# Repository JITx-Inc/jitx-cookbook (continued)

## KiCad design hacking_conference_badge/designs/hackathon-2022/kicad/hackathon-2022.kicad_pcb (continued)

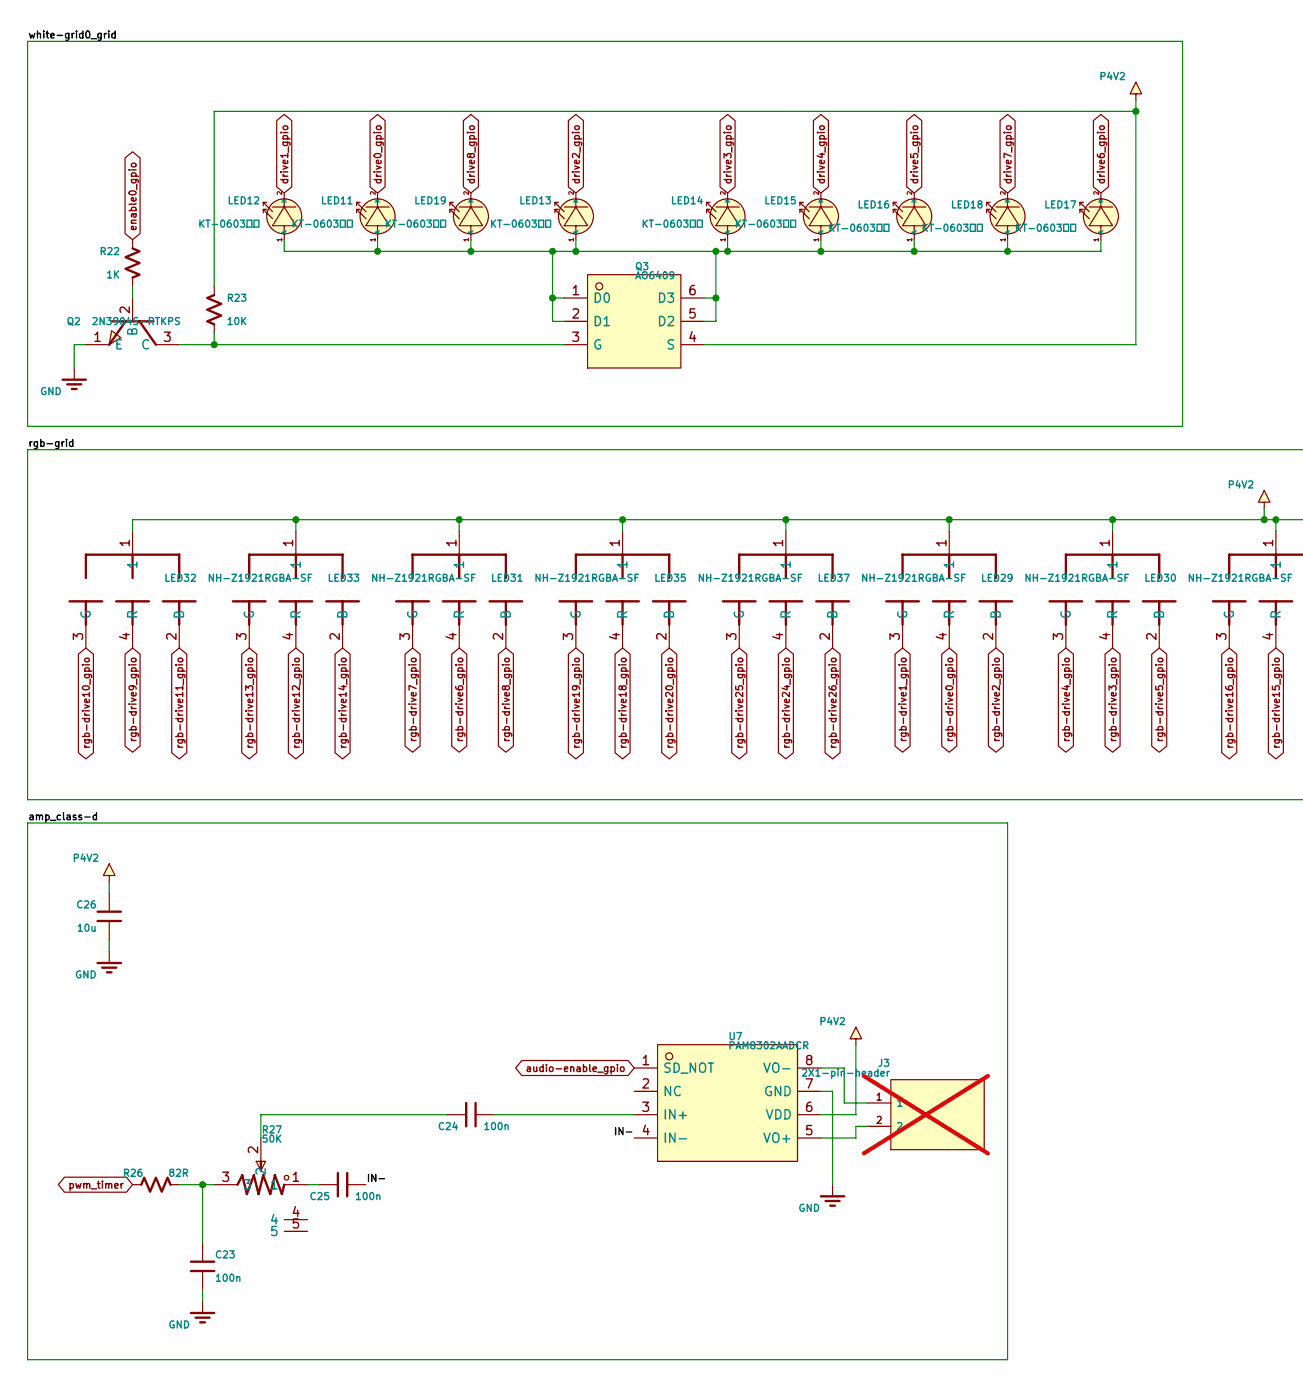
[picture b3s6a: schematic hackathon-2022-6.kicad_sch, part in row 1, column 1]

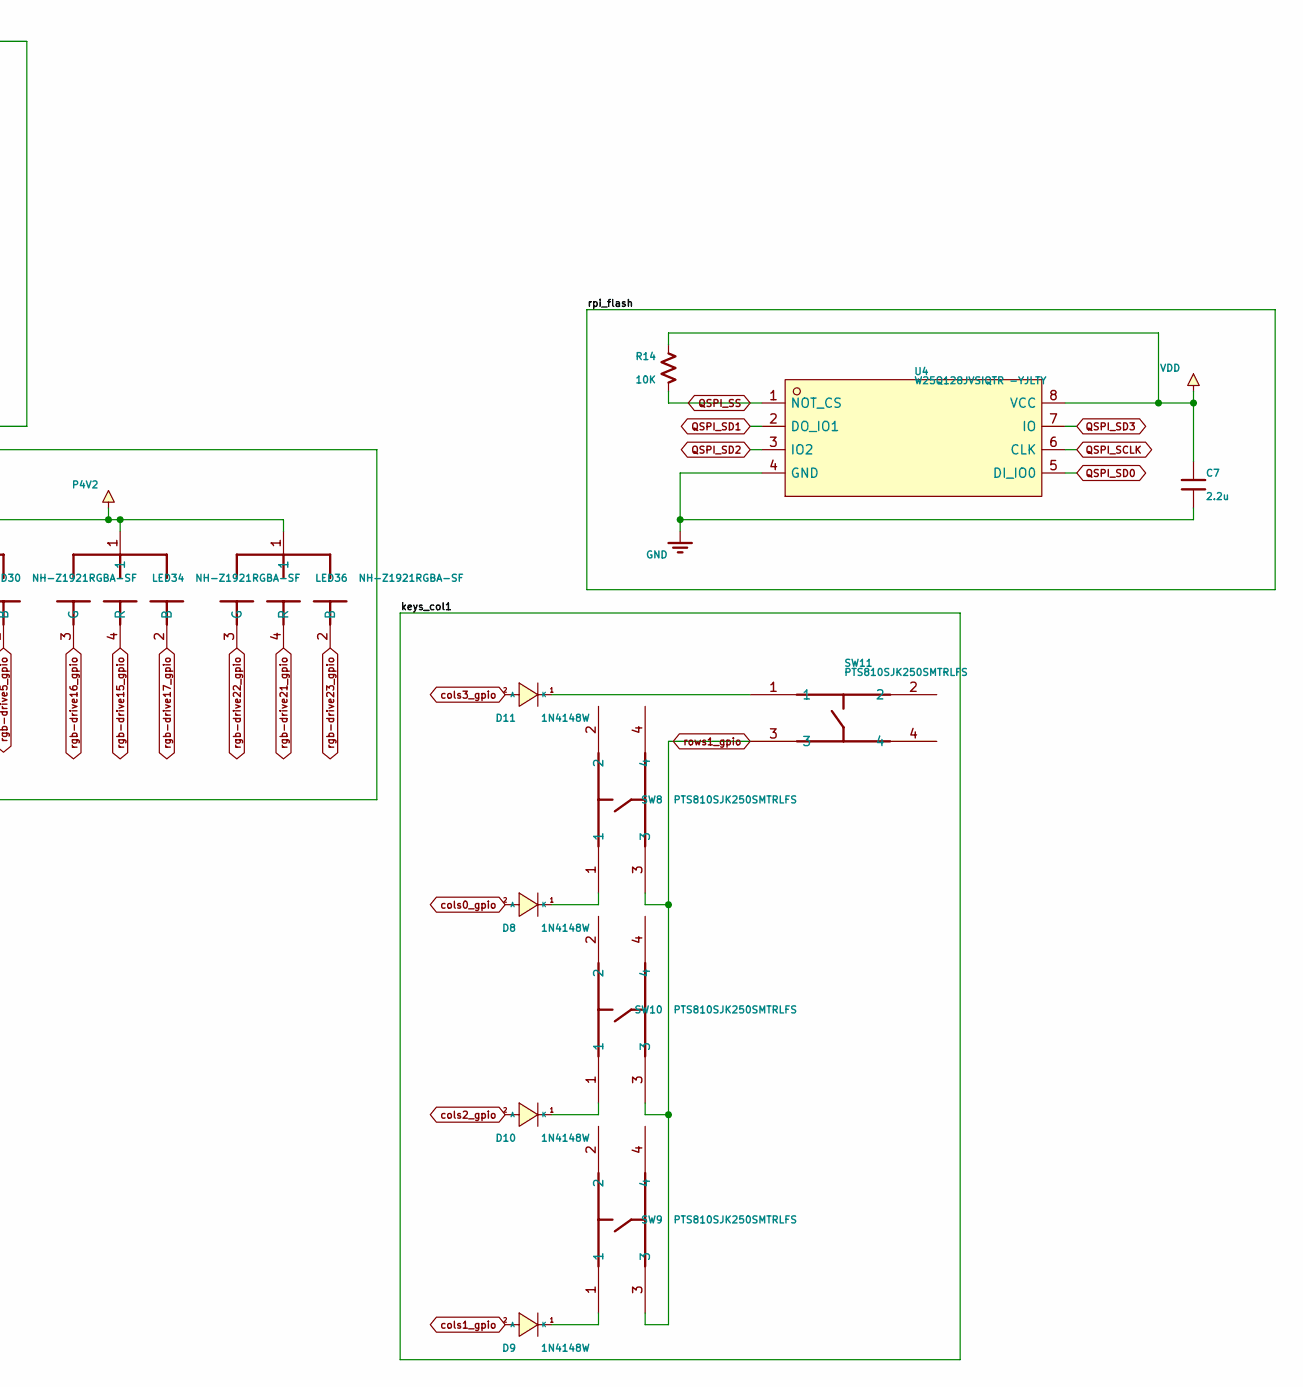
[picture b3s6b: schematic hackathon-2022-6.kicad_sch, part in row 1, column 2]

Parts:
C7: 2.2u; Pkg0402_5; MPN C1005X5R1E225K050BE
C23, C24, C25: 100n; Pkg0402_2; MPN CL05B104KA5NNNC
C26: 10u; Pkg0402_5; MPN CL05A106MP5NUNC
D8: 1N4148W; SOD_123F_L2_7_W1_6_LS3_8_RD_6; MPN 1N4148W; LCSC C81598
D9: 1N4148W; SOD_123F_L2_7_W1_6_LS3_8_RD_4; MPN 1N4148W; LCSC C81598
D10: 1N4148W; SOD_123F_L2_7_W1_6_LS3_8_RD_2; MPN 1N4148W; LCSC C81598
D11: 1N4148W; SOD_123F_L2_7_W1_6_LS3_8_RD_7; MPN 1N4148W; LCSC C81598
J3: 2X1-pin-header; PIN_GRID; MPN 2X1-pin-header; not fitted
LED11, LED12, LED13, LED14, LED15, LED16, LED17, LED18, LED19: KT-0603白灯; LED0603_R_RD_WHITE; MPN KT-0603白灯; LCSC C2290
LED29, LED30, LED31, LED32, LED33, LED34, LED35, LED36, LED37: NH-Z1921RGBA-SF; LED_ARRAY_SMD_4P_L2_2_W2_1_BR; MPN NH-Z1921RGBA-SF; LCSC C2874119
Q2: 2N3904S-RTKPS; SOT_23_3_L2_9_W1_3_P1_90_LS2_4_TR; MPN 2N3904S-RTKPS; LCSC C18536
Q3: AO6409; TSOP_6_L3_0_W1_5_P0_95_LS2_8_BR; MPN AO6409; LCSC C115833
R14: 10K; Pkg0402_1; MPN ESR01MZPJ103
R22: 1K; Pkg0402_1; MPN SG73P1EWTTP1001F
R23: 10K; Pkg0402_1; MPN RC1005F103CS
R26: 82R; Pkg0402_1; MPN RMCF0402FT82R0
R27: 50K; RES_TH_RK09K1130AAU_1; MPN RK09K1130ACL; LCSC C470291
SW8: PTS810SJK250SMTRLFS; KEY_SMD_4P_L4_2_W3_2_P2_20_LS4_6_1; MPN PTS810SJK250SMTRLFS; LCSC C221896
SW9: PTS810SJK250SMTRLFS; KEY_SMD_4P_L4_2_W3_2_P2_20_LS4_6_8; MPN PTS810SJK250SMTRLFS; LCSC C221896
SW10: PTS810SJK250SMTRLFS; KEY_SMD_4P_L4_2_W3_2_P2_20_LS4_6_6; MPN PTS810SJK250SMTRLFS; LCSC C221896
SW11: PTS810SJK250SMTRLFS; KEY_SMD_4P_L4_2_W3_2_P2_20_LS4_6_2; MPN PTS810SJK250SMTRLFS; LCSC C221896
U4: W25Q128JVSIQTR -YJLTY; SOIC_8_L5_3_W5_3_P1_27_LS8_0_BL; MPN W25Q128JVSIQTR -YJLTY; LCSC C2921483
U7: PAM8302AADCR; SOP_8_L4_9_W3_9_P1_27_LS6_0_BL; MPN PAM8302AADCR; LCSC C112137

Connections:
/6: rpi_flash/IN-: C25.2, U7.4 (IN-)
GND: C7.2, C23.2, C26.1, Q2.1 (E), U4.4 (GND), U7.7 (GND); also elsewhere on the board
unnamed: C23.1, R26.2, R27.3
unnamed: C24.1, R27.2
unnamed: C25.1, R27.1
unnamed: D8.1 (K), SW8.1
unnamed: D9.1 (K), SW9.1
unnamed: D10.1 (K), SW10.1
unnamed: D11.1 (K), SW11.1
unnamed: LED11.1 (A), LED12.1 (A), LED13.1 (A), LED14.1 (A), LED15.1 (A), LED16.1 (A), LED17.1 (A), LED18.1 (A), LED19.1 (A), Q3.1 (D0), Q3.2 (D1), Q3.5 (D2), Q3.6 (D3)
unnamed: Q2.2 (B), R22.2
unnamed: Q2.3 (C), Q3.3 (G), R23.1
unnamed: C24.2, U7.3 (IN+)
unnamed: J3.2, U7.5 (VO+)
unnamed: J3.1, U7.8 (VO-)
P4V2: C26.2, LED29.1, LED30.1, LED31.1, LED32.1, LED33.1, LED34.1, LED35.1, LED36.1, LED37.1, Q3.4 (S), R23.2, U7.6 (VDD); also elsewhere on the board
QSPI_SCLK: U4.6 (CLK); also elsewhere on the board
QSPI_SD0: U4.5 (DI_IO0); also elsewhere on the board
QSPI_SD1: U4.2 (DO_IO1); also elsewhere on the board
QSPI_SD2: U4.3 (IO2); also elsewhere on the board
QSPI_SD3: U4.7 (IO); also elsewhere on the board
QSPI_SS: R14.2, U4.1 (NOT_CS); also elsewhere on the board
VDD: C7.1, R14.1, U4.8 (VCC); also elsewhere on the board
audio-enable_gpio: U7.1 (SD_NOT); also elsewhere on the board
cols0_gpio: D8.2 (A); also elsewhere on the board
cols1_gpio: D9.2 (A); also elsewhere on the board
cols2_gpio: D10.2 (A); also elsewhere on the board
cols3_gpio: D11.2 (A); also elsewhere on the board
drive0_gpio: LED11.2 (K); also elsewhere on the board
drive1_gpio: LED12.2 (K); also elsewhere on the board
drive2_gpio: LED13.2 (K); also elsewhere on the board
drive3_gpio: LED14.2 (K); also elsewhere on the board
drive4_gpio: LED15.2 (K); also elsewhere on the board
drive5_gpio: LED16.2 (K); also elsewhere on the board
drive6_gpio: LED17.2 (K); also elsewhere on the board
drive7_gpio: LED18.2 (K); also elsewhere on the board
drive8_gpio: LED19.2 (K); also elsewhere on the board
enable0_gpio: R22.1; also elsewhere on the board
pwm_timer: R26.1; also elsewhere on the board
rgb-drive0_gpio: LED29.4 (R); also elsewhere on the board
rgb-drive1_gpio: LED29.3 (G); also elsewhere on the board
rgb-drive2_gpio: LED29.2 (B); also elsewhere on the board
rgb-drive3_gpio: LED30.4 (R); also elsewhere on the board
rgb-drive4_gpio: LED30.3 (G); also elsewhere on the board
rgb-drive5_gpio: LED30.2 (B); also elsewhere on the board
rgb-drive6_gpio: LED31.4 (R); also elsewhere on the board
rgb-drive7_gpio: LED31.3 (G); also elsewhere on the board
rgb-drive8_gpio: LED31.2 (B); also elsewhere on the board
rgb-drive9_gpio: LED32.4 (R); also elsewhere on the board
rgb-drive10_gpio: LED32.3 (G); also elsewhere on the board
rgb-drive11_gpio: LED32.2 (B); also elsewhere on the board
rgb-drive12_gpio: LED33.4 (R); also elsewhere on the board
rgb-drive13_gpio: LED33.3 (G); also elsewhere on the board
rgb-drive14_gpio: LED33.2 (B); also elsewhere on the board
rgb-drive15_gpio: LED34.4 (R); also elsewhere on the board
rgb-drive16_gpio: LED34.3 (G); also elsewhere on the board
rgb-drive17_gpio: LED34.2 (B); also elsewhere on the board
rgb-drive18_gpio: LED35.4 (R); also elsewhere on the board
rgb-drive19_gpio: LED35.3 (G); also elsewhere on the board
rgb-drive20_gpio: LED35.2 (B); also elsewhere on the board
rgb-drive21_gpio: LED36.4 (R); also elsewhere on the board
rgb-drive22_gpio: LED36.3 (G); also elsewhere on the board
rgb-drive23_gpio: LED36.2 (B); also elsewhere on the board
rgb-drive24_gpio: LED37.4 (R); also elsewhere on the board
rgb-drive25_gpio: LED37.3 (G); also elsewhere on the board
rgb-drive26_gpio: LED37.2 (B); also elsewhere on the board
rows1_gpio: SW8.3, SW9.3, SW10.3, SW11.3; also elsewhere on the board

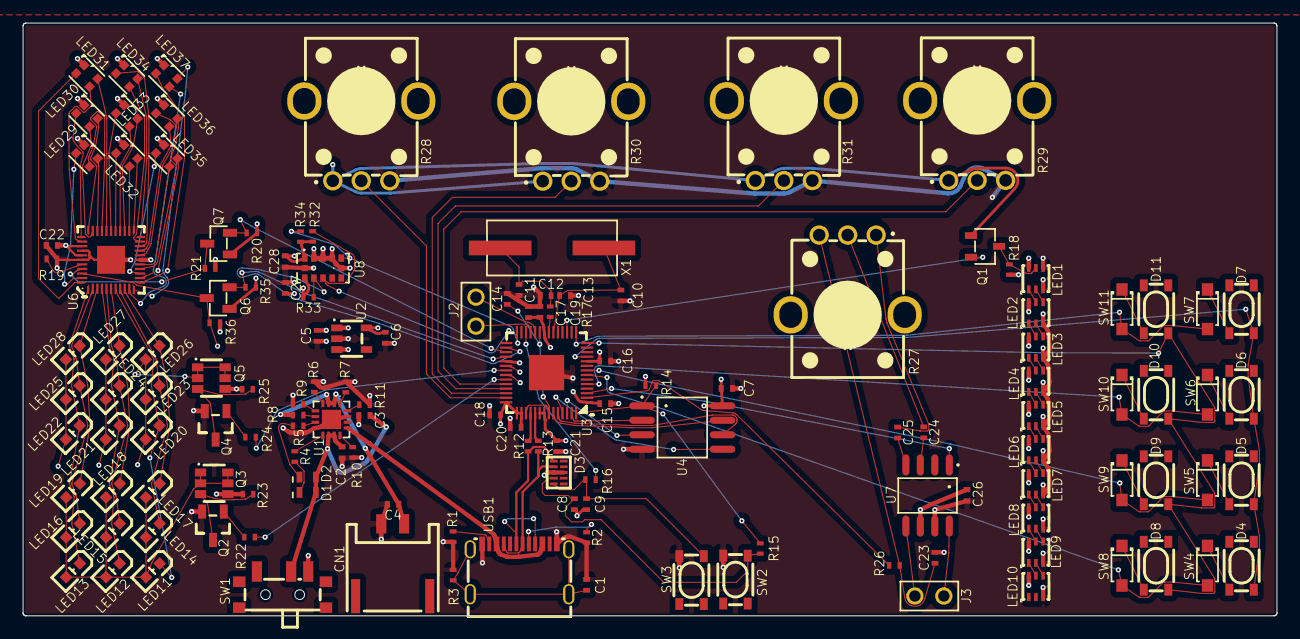
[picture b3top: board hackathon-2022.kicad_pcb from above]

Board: 6 copper layers, 110.0 x 52.0 mm, 142 parts (0 on the bottom side), 137 nets.

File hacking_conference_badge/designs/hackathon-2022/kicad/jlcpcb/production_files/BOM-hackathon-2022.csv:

Comment,Designator,Footprint,LCSC
TAXM12M2GLFBET2T,X1,HC_49S_L11_4_W4_8,C111117
PAM8302AADCR,U7,SOP_8_L4_9_W3_9_P1_27_LS6_0_BL,C112137
AO6409,"Q3,Q5",TSOP_6_L3_0_W1_5_P0_95_LS2_8_BR,C115833
BSN20,Q1,SOT_23_3_L2_9_W1_6_P1_90_LS2_8_BR,C116157
AP2125K-2.8TRG1,U2,SOT_23_5_L3_0_W1_7_P0_95_LS2_8_BR,C176952
2N3904S-RTKPS,"Q2,Q4",SOT_23_3_L2_9_W1_3_P1_90_LS2_4_TR,C18536
PTS810SJK250SMTRLFS,"SW10,SW11,SW2,SW3,SW4,SW5,SW6,SW7,SW8,SW9",KEY_SMD_4P_L4_2_W3_2_P2_20_LS4_6_6,C221896
KT-0603白灯,"LED11,LED12,LED13,LED14,LED15,LED16,LED17,LED18,LED19,LED20,LED21,LED22,LED23,LED24,LED25,LED26,LED27,LED28",LED0603_R_RD_WHITE,C2290
IS31FL3236A-QFLS2-TR,U6,C246443,C246443
NH-Z1921RGBA-SF,"LED29,LED30,LED31,LED32,LED33,LED34,LED35,LED36,LED37",LED_ARRAY_SMD_4P_L2_2_W2_1_BR,C2874119
W25Q128JVSIQTR -YJLTY,U4,SOIC_8_L5_3_W5_3_P1_27_LS8_0_BL,C2921483
PUSB3FR4,D3,DFN2510A_10_L2_5_W1_0_P0_50_BL,C294620
50K,"R27,R28,R29,R30,R31",RES_TH_RK09K1130AAU_1,C470291
BQ24078RGTR,U1,VQFN_16_L3_0_W3_0_P0_50_BL_EP,C473396
PH2.0-2PWB Horizontal,CN1,CONN_SMD_2P_P2_00_PH2_0_SPWB,C47647
TYPE-C-31-M-23,USB1,USB_C_SMD_TYPE_C_31_M_23,C530613
BSS138,"Q6,Q7",SOT_23_3_L2_9_W1_3_P1_90_LS2_4_BR,C713688
MK-12C02-G025,SW1,SW_SMD_MK_12C02_G025,C778186
1N4148W,"D10,D11,D4,D5,D6,D7,D8,D9",SOD_123F_L2_7_W1_6_LS3_8_RD_2,C81598
VL53L0CXV0DH1,U8,OPTO_SMD_12P_VL53L0CXV0DH_1,C91199
WS2816C-2121,"LED1,LED10,LED2,LED3,LED4,LED5,LED6,LED7,LED8,LED9",LED_SMD_6P_L2_2_W2_2_TL_1,C965561
1K,R4,Pkg0402_6,
33R,R8,Pkg0402_6,
2.2u,C7,Pkg0402_5,
10K,R35,Pkg0402_1,
10K,R23,Pkg0402_1,
100n,C27,Pkg0402_2,
100n,C1,Pkg0402_2,
2K,R5,Pkg0402_6,
1u,C5,Pkg0402_2,
33R,R9,Pkg0402_6,
1K,R24,Pkg0402_1,
1u,C18,Pkg0402_2,
10K,R14,Pkg0402_1,
30p,C10,Pkg0402_2,
1u,C14,Pkg0402_2,
10K,R36,Pkg0402_1,
10K,R25,Pkg0402_1,
1u,C6,Pkg0402_2,
1u,C16,Pkg0402_2,
10K,R20,Pkg0402_1,
100n,C23,Pkg0402_2,
"green, Vf 2.0, If 20 mA",D2,Pkg0603,
5K1,R1,Pkg0402_1,
1K1,R10,Pkg0402_4,
RP2040,U3,C2040,
27R,R12,Pkg0402_1,
30p,C11,Pkg0402_2,
1u,C15,Pkg0402_2,
1u,C19,Pkg0402_2,
10u,C26,Pkg0402_5,
1K,R17,Pkg0402_4,
10K,R21,Pkg0402_1,
100n,C24,Pkg0402_2,
5K1,R2,Pkg0402_1,
4.7u,C3,Pkg0402,
2K7,R11,Pkg0402_1,
27R,R13,Pkg0402_1,
100n,C8,Pkg0402_2,
1u,C21,Pkg0402_2,
30p,C12,Pkg0402_2,
33R,R6,Pkg0402_6,
1K,R16,Pkg0402_4,
82R,R26,Pkg0402_1,
8K2,R32,Pkg0402_3,
1u,C20,Pkg0402_2,
1K,R18,Pkg0402_4,
100n,C25,Pkg0402_2,
"red, Vf 2.0, If 20 mA",D1,Pkg0603,
3K3,R19,Pkg0402_1,
8K2,R34,Pkg0402_3,
30p,C13,Pkg0402_2,
8K2,R33,Pkg0402_3,
10K,R7,Pkg0402_6,
1u,C17,Pkg0402_2,
4.7u,C2,Pkg0402,
1K,R15,Pkg0402_4,
100n,C9,Pkg0402_2,
4.7u,C28,Pkg0402_5,
100K,R3,Pkg0402_1,
4.7u,C4,Pkg0402,
2.2u,C22,Pkg0402_5,
1K,R22,Pkg0402_1,

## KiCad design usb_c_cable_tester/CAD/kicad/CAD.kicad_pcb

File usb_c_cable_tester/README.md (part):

# USB-C Cable Tester PCB Cookbook Recipe

This tutorial guides you in creating a USB-C cable testing PCB in JITX from the ground up. With step-by-step instructions, even individuals with no prior experience in JITX can learn to define hardware in software and generate a PCB using code.

## Getting started
##### Prerequisites
To start, we'll need to setup JITX. We can follow this tutorial to get setup: https://docs-testing.jitx.com/faq/installationinstructions.html

Then, we need to create a new project. So let's run VSCode, select the JITX extension, and click "New Project".

Now we're ready to start designing the board.

> NOTE: The code below is not the entire design. Refer to the [Github repo](https://github.com/JITx-Inc/jitx-cookbook/tree/main/usb_c_cable_tester) for a full working design. Below, we describe the design flow and thought process behind designing this board.

##### Intended functionality
Let's start by considering what we want our design to be able to do. It needs to to test every connection in a USB-C cable, and provide feedback about what connections exist, and what connections don't exist, or are broken. To do that, we'll design a circuit board which:

- connects to both ends of a USB-C cable
- sends a signal into the pins of one connector of the cable and should be present on the pins of the other connector
- measures that signal using an LED indicator for every individual USB-C pin. If the LED doesn't light up, it means that the cable has a bad connection

##### Implementation plan

To accomplish the above, we need a few components:

- 2x USB-C connectors, we'll use the [
1054500101 USB-C connector](https://www.lcsc.com/product-detail/span-style-background-color-ff0-USB-span-span-style-background-color-ff0-Connectors-span_MOLEX-1054500101_C134092.html)
- a coin cell battery clip (or similiar battery holder), we'll use the [CR2032 SMD coin cell clip](https://datasheet.lcsc.com/lcsc/1811061923_Q-J-CR2032-BS-6-1_C70377.pdf)
- a number of indicator LEDs

Considering this is a simple design, we'll use a 2 layer board, with all components on the same side for ease of PCBA.

##### Resources

This board is fully open source, available here: [USB-C Cable Tester Recipe](https://github.com/JITx-Inc/jitx-cookbook/tree/main/usb_c_cable_tester)

Clone [this repo](https://github.com/JITx-Inc/jitx-cookbook) and open the subfolder `usb_c_cable_tester` in VSCode to follow along.

## Components

We've identified some specific components that we want to use, namely the [
1054500101 USB-C Connector](https://www.lcsc.com/product-detail/span-style-background-color-ff0-USB-span-span-style-background-color-ff0-Connectors-span_MOLEX-1054500101_C134092.html) and the [CR2032-BS-6-1 Coin Cell Battery Clip](https://jlcpcb.com/partdetail/QJ-CR2032_BS_61/C70377), alongside some other components.

JITX has built-in support for many basic components like capacitors, resistors, and LED's, so we'll be able to source those as we need them while designing. For the specific ICs we're using, we'll need to either find an existing component definition, or make that ourselves.

##### Battery Clip

To power the design, we'll need an on-board battery. Since this is a low-power, low-cost, rarely used board, we want to use a battery than will last a long time. A 3V lithium coin cell is a good choice here. Fortunately, [OCDB](https://github.com/JITx-Inc/open-components-database) already contains a definition of a coin cell battery clip, the [CR2032-BS-6-1](https://jlcpcb.com/partdetail/QJ-CR2032_BS_61/C70377). We found this by opening OCDB in VS Code, pressing `Ctrl + Shift + F`, and then searching for "battery".

Let's go ahead an instantiate that battery clip holder inside our top level `pcb-module`. We can create it, connect it, and place it in a few lines of code:
```
  ; create a coin cell battery
  val battery-capacity = 90.0 ;set the capacity of battery, in mAh
  inst battery : ocdb/components/q-n-j/CR2032-BS-6-1/component(battery-capacity); create a battery with the specified capacity
  net (POWER battery.power.vdd); connect positive of battery to the POWER net
  net (GND battery.power.gnd); connect negative of battery to the GND net
  val battery-y = board-height / 3.5; programmatically calculate an x and y position of the battery based on the board-shape
  val battery-x = board-width / -7.0; 
  place(battery) at loc(battery-x, battery-y, 90.0) on Top; place the battery on the top of the board at the calculated position
```

##### LEDs

We also want to build a circuit generator that picks specific colors of LEDs, so we'll use the Everlight Electronics family of 0603 Chip LEDs, which all have similar curves for luminous intensity versus current. For example, here's the [red Everlight Electronics 0603 LED](https://datasheet.lcsc.com/lcsc/1810010118_Everlight-Elec-19-21-R6C-FP1Q2L-3T_C93128.pdf).

For now, we'll simply identify that we want to use a few different colors of LEDs in the same family, and create a component generator that selects the correct LED based on our color parameter:
```
public pcb-component led-component (color:LED-COLORS) :
  name = "LED-maker-ROYGBIV"
  description = "Everlight Elec 0603 various color SMD LEDs"
  manufacturer = "Everlight Elec"
  reference-prefix = "LED"
  property(self.package) = "0603"

  ; properties shared by all LEDs
  property(self.max-current) = 25.0e-3
  property(self.rated-temperature) = 85.0

  ; properties different among LEDs
  switch(color) :
    RED:
      mpn = "19-21/R6C-FP1Q2L/3T"
      property(self.LCSC) = "C93128"
      property(self.datasheet) = "https://datasheet.lcsc.com/lcsc/1810010118_Everlight-Elec-19-21-R6C-FP1Q2L-3T_C93128.pdf"
      property(self.li) = min-max(45.0e-3, 112.0e-3)
      property(self.vf) = min-max(1.7, 2.3)
    ORANGE:
      mpn = "19-217UYOC/S3077/TR8"
      property(self.LCSC) = "C264474"
      property(self.datasheet) = "https://datasheet.LCSC.com/lcsc/1912111437_Everlight-Elec-19-217UYOC-S3077-TR8_C264474.pdf"
      property(self.li) = min-max(28.0e-3, 72.0e-3)
      property(self.vf) = min-max(1.7, 2.4)
    YELLOW:
      mpn = "19-21/Y2C-CN1P2B/3T"
      property(self.LCSC) = "C131265"
      property(self.datasheet) = "https://datasheet.LCSC.com/lcsc/1811141628_Everlight-Elec-19-21-Y2C-CN1P2B-3T_C131265.pdf"
      property(self.li) = min-max(28.5e-3, 72.0e-3)
      property(self.vf) = min-max(1.75, 2.35)
    GREEN:
      mpn = "19-217/GHC-YN1P2B18X/3T"
      property(self.LCSC) = "C2980184"
      property(self.datasheet) = "https://datasheet.LCSC.com/lcsc/2202101201_Everlight-Elec-19-21-GHC-YR1S2-3T_C2973113.pdf"
      property(self.li) = min-max(28.5e-3, 72.0e-3)
      property(self.vf) = min-max(2.7, 3.7)
    BLUE:
      mpn = "19-213/BHC-AP2Q2E/3T"
      property(self.LCSC) = "C474027"
      property(self.datasheet) = "https://datasheet.LCSC.com/lcsc/1912251011_Everlight-Elec-19-213-BHC-AP2Q2E-3T_C474027.pdf"
      property(self.li) = min-max(57.0e-3, 112.0e-3)
      property(self.vf) = min-max(2.75, 3.65)

  pin-properties :
    [pin:Ref    | pads:Int ... | side:Dir ]
    [a          | 1            | Up       ]
    [c          | 2            | Down     ]

  assign-symbol(diode-sym(DiodeLED))
  assign-landpattern(lp-led-maker)

```

Now all we have to do is change the color argument, and we will instantiate the correct LED - no need to keep loading datasheets and searching suppliers, we just do that once, turn it into code, and reuse the same component with no extra effort.
##### USB-C Connector

We also need two USB-C connectors that the two ends of our female-to-female USB-C cable will plug into. One thing to ensure is that the USB-C connector that we select doesn't internally bridge connections, as we want to be able to test each connection in the USB-C cable individually.

We originally selected the [U263-241N-4BQC11-1](https://www.lcsc.com/product-detail/USB-Connectors_XKB-Connectivity-U263-241N-4BQC11-1_C381139.html) connector,  but it was out of stock by the time we went to order. JITX made it easy to swap that out for a different in-stock connector, the Molex [1054500101](https://www.lcsc.com/product-detail/span-style-background-color-ff0-USB-span-span-style-background-color-ff0-Connectors-span_MOLEX-1054500101_C134092.html) USB-C Connector.

Now that the USB-C connector is in our project, we can instantiate it and programmatically place it at the board's edge:
```
  ; create USB connectors
  val usb-x-shift = 4.0
  val usb-y-shift = -7.0
  ; OLD CONNECTOR -> public inst in-usb : ocdb/components/xkb/U263-241N-4BQC11-1/component
  public inst in-usb : components/USB-C-1054500101/component
  place(in-usb) at loc((-1.0 * width(board-shape) / 2.0) + usb-x-shift, usb-y-shift, -90.0) on Top
  ; OLD CONNECTOR -> public inst out-usb : ocdb/components/xkb/U263-241N-4BQC11-1/component
  public inst out-usb : components/USB-C-1054500101/component
  place(out-usb) at loc((width(board-shape) / 2.0) - usb-x-shift, usb-y-shift, 90.0) on Top
```

We downloaded this [USB-C connector from SnapEDA](https://www.snapeda.com/parts/1054500101/Molex/view-part) and imported it directly into our project.

## Design 
##### Circuit Generator - LED indicator modules
We want all of our LEDs to have the same brightness, but each LED will need a different driving current to achieve an identical brightness. In the past, we might have worked this out on paper or in a spreadsheet. 

We can incorporate these calculations directly into the code and reuse that everytime we instantiate a new LED. So, let's make a circut generator which creates an LED and a properly selected ballast resistor. We'll choose the ballast resistor given a color and a required brightness.

First, we'll create a module that accepts a color and an input voltage: 

```
; the LED and ballast resistor module
public pcb-module module (color:LED-COLORS, voltage-in:Toleranced) :
```
Then, we create an LED of the given color:
```
  inst led : components/LED-maker-ROYGB/led-component(color)
```
We then create a ballast resistor of the proper resistance for a given brightness (here, 50 millicandellas):

```
  ; create ballast resistor
  val brightness = 50.0e-3 ; candella
  val ballast-resistance = compute-ballast-resistor(led, voltage-in, brightness);
  inst ballast-res : database-part(["category" => "resistor", "resistance" => ballast-resistance, "case" => ["0402"], "_exist" => ["vendor_part_numbers.lcsc"]])
```

The automation capability here comes from two function calls. First, we wrote a custom function that maps from an LED parameters, input voltage, and brightness to a ballast resistor resistance:

```
defn compute-ballast-resistor (led:JITXObject, voltage:Toleranced, brightness:Double) -> Double : ; led is an led-component, brightness is in candellas
  ; nominal luminous intensity of this LED
  val nli = center-value(property(led.li))
  val vf = center-value(property(led.vf))

  ; map luminous intensity to current
  ; Datasheet gives data in tables, so use piecewise linear model to find value
  val my-pwl = PWL([
      [0.02 * nli, 1.0e-3] 
      [0.06 * nli, 2.0e-3]
      [0.5 * nli, 10.0e-3]
      [1.0 * nli, 20.0e-3]
    ])
  val computed-current = my-pwl[brightness]

  ; get the required resistance, given the input voltage and the desired current
  val computed-resistance = (voltage - typ(vf)) / typ(computed-current)
  ; turn the resistor into the closest standard value resistor by passing in the resistance that we computed
  closest-std-val(typ-value(computed-resistance), 5.0)
```

Then we used the built-in JITX parts database to parametrically search and find a resistor that matches our resistance, package size, and supplier needs:
```
database-part(["category" => "resistor", "resistance" => ballast-resistance, "case" => ["0402"], "_exist" => ["vendor_part_numbers.lcsc"]])
```

The above `database-part` query contains _millions of parts_ that you can parametrically define using category, value, manufacturer, MPN, etc. This system can greatly increase your productivity by automatically finding parts and importing their information (MPN, manufacturer, VPN, etc.). We can filter based on live data about components stock from various sources, so our design only includes components that are guaranteed to be available.

This generates a `pcb-module` with LED and properly tuned ballast resistor, already connected and ready to drop into our design. Now in the future, whenever we need a brightness controlled, colored indicator LED, we can reuse this module.

##### Board Setup
We've now created many components and circuit generators that will serve as the foundation of our design. In the top level module, let's now setup our board, connect things together, and add a bit of organization so our design is ready for export.

First, we create a `pcb-module`, define our input/output pins, add version label text, and place a logo on the silkscreen:
```
pcb-module usb_c_cable_tester_module :
  ; define pins to expose from our module
  port gnd
  port power

  ; define nets
  net GND (gnd)
  net POWER (power)

  ; draw a version number and date on the board silkscreen
  val mydate:String = get-time-string("%Y-%m-%d")
  inst version-label  : ocdb/artwork/board-text/version-silkscreen(to-string("USB-C Cable Tester | Version 0.1 %_" % [get-time-string("%Y-%m-%d")])) ; make a version label text on silkscreen
  place(version-label) at loc(0.0, height(board-shape) / 2.0 - 1.0) on Bottom ; place the version label text at specified location

  ; setup logo
  inst logo : ocdb/artwork/jitx-logo/logo(10.0)
  place(logo) at loc(10.0, -5.0, 0.0) on Bottom
  component-status(logo) :
  bom-status : NotInBOM

```

##### Naming test points based on connected net - circuit design introspection

Often, we want to have more control of our components and design. The goal is to automate engineering best practices like having testpoints with informative names.

```
; place a testpoint
defn my-testpoint-strap (tp:JITXObject, tp-name:String, diameter:Double) -> JITXObject:
  inside pcb-module :
    ...
```

First, we created the testpad with `public inst tp-pad : gen-testpad(diameter)`. We then connect it to the net or pin provided using `net (tp-pad.p tp)`. Finally, we set the value of the testpad and place its label in a convenient location:
```
    ; name the test point
    value-label(tp-pad) = Text(tp-name, 1.0, W, loc(1.2, 0.0))
    ; val my-label = Text(tp-name, 1.0, W, loc(1.5, 0.0))
    inst my-label : ocdb/artwork/board-text/text(tp-name, 1.0, 0.0)
    place(my-label) at loc(1.2, -0.4, 0.0) on Top (relative-to tp-pad)
    tp-pad
```
We now have a testpoint creation function, which we can reuse anywhere we need a testpoint, in this project or in others.

##### Connecting Everything
We already setup the board, instantiated and connected the battery clip and USB-C connector, and wrote circuit generators, as discussed above.

Now, let's connect everything together into a single design.

Since we want to test every individual connection in the USB-C cable, let's create a net for every pin in our output-usb connector:

```
  ; make nets for all of the pins on the usb C that we want to test
  net VBUS (out-usb.usb-c-pinout.VBUS) ; for each pin of the USB, we make a net
  net GND-usb (out-usb.usb-c-pinout.GND)
  net SHIELD (out-usb.usb-c-pinout.shield)
  net SBU2 (out-usb.usb-c-pinout.SBU2)
  net SBU1 (out-usb.usb-c-pinout.SBU1)
  net DN2 (out-usb.usb-c-pinout.DN2)
  net DP2 (out-usb.usb-c-pinout.DP2)
  net DN1 (out-usb.usb-c-pinout.DN1)
  net DP1 (out-usb.usb-c-pinout.DP1)
  net CC2 (out-usb.usb-c-pinout.CC2)
  net CC1 (out-usb.usb-c-pinout.CC1)
  net SSTXP1 (out-usb.usb-c-pinout.SSTXP1)
  net SSTXN1 (out-usb.usb-c-pinout.SSTXN1)
  net SSRXP1 (out-usb.usb-c-pinout.SSRXP1)
  net SSRXN1 (out-usb.usb-c-pinout.SSRXN1)
  net SSTXP2 (out-usb.usb-c-pinout.SSTXP2)
  net SSTXN2 (out-usb.usb-c-pinout.SSTXN2)
  net SSRXP2 (out-usb.usb-c-pinout.SSRXP2)
  net SSRXN2 (out-usb.usb-c-pinout.SSRXN2)
```

However, that's a tad cumbersome. We can do the exact same thing in a loop:
```
  for p in pins(out-usb) do :
    val pin-ref = ref(p)
    val pin-name = tail(pin-ref, ref-length(pin-ref) - 1)
    make-net(to-symbol(pin-name), [p])
```

That's much cleaner and more extendable.

We then order the pins of the USB based on their physical location, map those pins to the nets we just created, and generate a test LED module for every pin:
```
  ; get all pins of the USB, and order them based on how they physically appear
  val ordered-pins = get-pins-physically-ordered(out-usb)

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
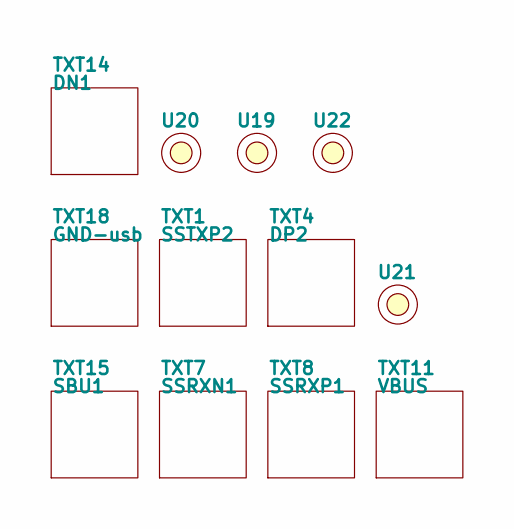
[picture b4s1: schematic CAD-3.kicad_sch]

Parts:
TXT1: SSTXP2; TEXT_LP_1; MPN SSTXP2
TXT4: DP2; TEXT_LP_11; MPN DP2
TXT7: SSRXN1; TEXT_LP_12; MPN SSRXN1
TXT8: SSRXP1; TEXT_LP_18; MPN SSRXP1
TXT11: VBUS; TEXT_LP_8; MPN VBUS
TXT14: DN1; TEXT_LP_14; MPN DN1
TXT15: SBU1; TEXT_LP_2; MPN SBU1
TXT18: GND-usb; TEXT_LP_9; MPN GND-usb
U19, U20, U21, U22: NPTH

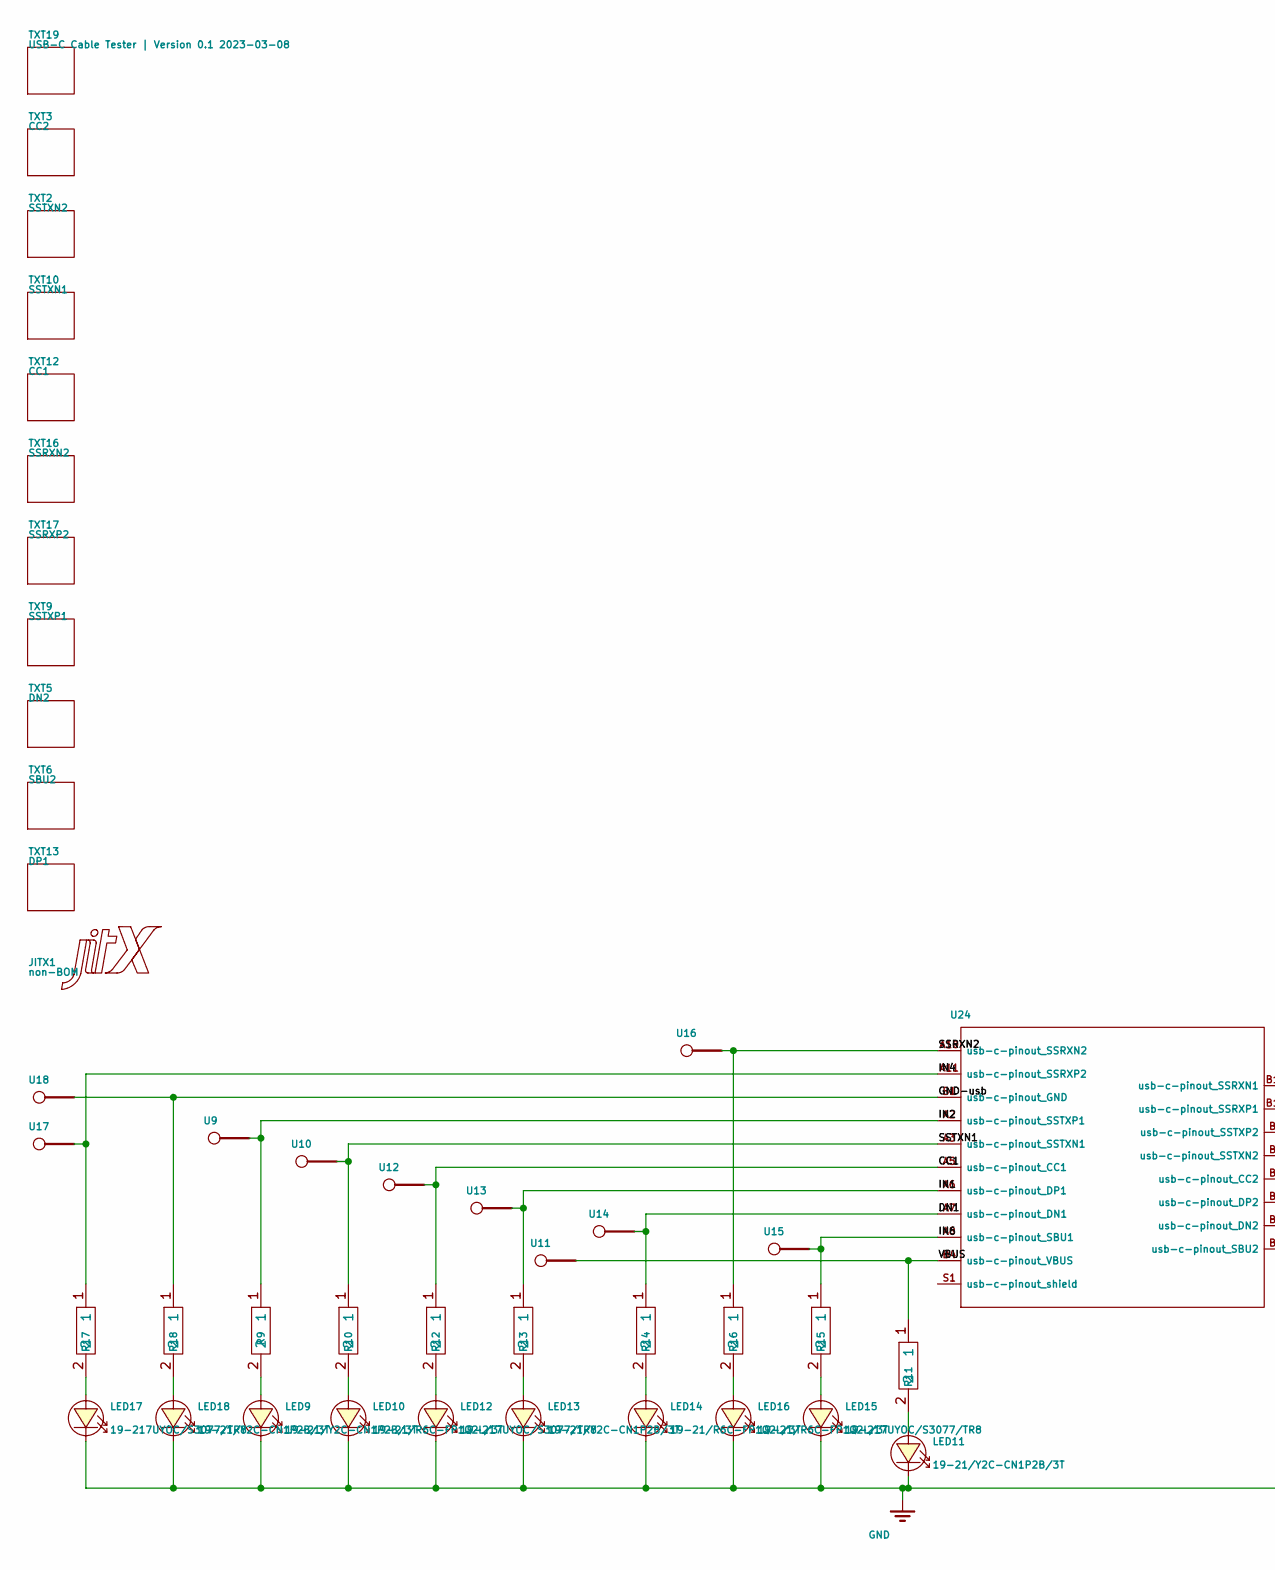
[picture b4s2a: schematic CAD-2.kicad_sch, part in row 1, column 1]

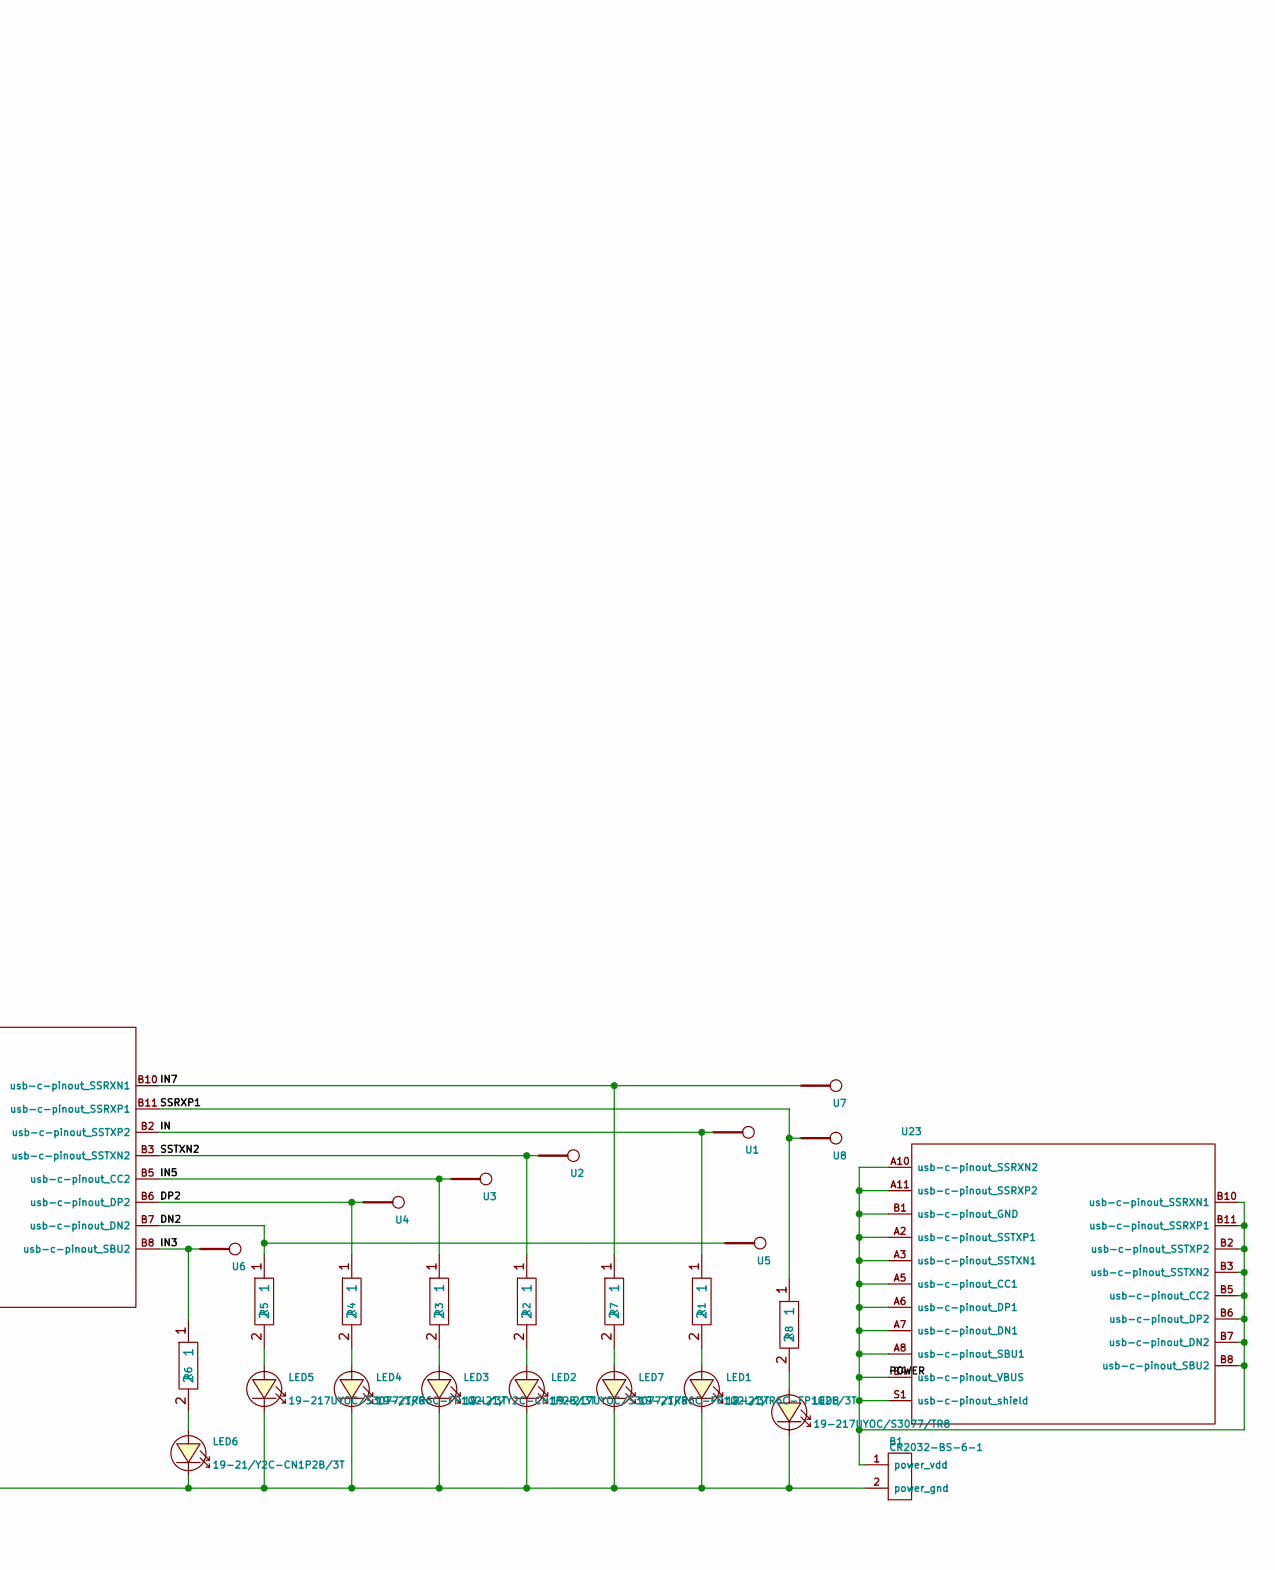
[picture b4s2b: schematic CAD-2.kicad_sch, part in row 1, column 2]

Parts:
B1: CR2032-BS-6-1; CR2032_BS_6_1_LANDPATTERN; MPN CR2032-BS-6-1; LCSC C70377
JITX1: non-BOM; JITX_SM_LP; MPN non-BOM
LED1, LED4, LED7, LED10, LED14, LED16: 19-21/R6C-FP1Q2L/3T; Pkg0603; MPN 19-21/R6C-FP1Q2L/3T; LCSC C93128
LED2, LED5, LED8, LED12, LED15, LED17: 19-217UYOC/S3077/TR8; Pkg0603; MPN 19-217UYOC/S3077/TR8; LCSC C264474
LED3, LED6, LED9, LED11, LED13, LED18: 19-21/Y2C-CN1P2B/3T; Pkg0603; MPN 19-21/Y2C-CN1P2B/3T; LCSC C131265
R1, R4, R7, R10, R14, R16: R_0402_1005Metric; MPN 0402WGJ0750TCE; LCSC C25180
R2, R3, R5, R6, R8, R9, R11, R12, R13, R15, R17, R18: R_0402_1005Metric; MPN RS-02K470JT; LCSC C1096
TXT2: SSTXN2; TEXT_LP_4; MPN SSTXN2
TXT3: CC2; TEXT_LP_10; MPN CC2
TXT5: DN2; TEXT_LP_17; MPN DN2
TXT6: SBU2; TEXT_LP_5; MPN SBU2
TXT9: SSTXP1; TEXT_LP_6; MPN SSTXP1
TXT10: SSTXN1; TEXT_LP_13; MPN SSTXN1
TXT12: CC1; TEXT_LP; MPN CC1
TXT13: DP1; TEXT_LP_7; MPN DP1
TXT16: SSRXN2; TEXT_LP_16; MPN SSRXN2
TXT17: SSRXP2; TEXT_LP_3; MPN SSRXP2
TXT19: USB-C Cable Tester | Version 0.1 2023-03-08; TEXT_LP_15; MPN USB-C Cable Tester | Version 0.1 2023-0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
U1, U2, U3, U4, U5, U6, U7, U8, U9, U10, U11, U12, U13, U14, U15, U16, U17, U18: TESTPAD
U23, U24: MOLEX10545001011

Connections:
/2: /CC1: R12.1, U12.tp (p), U24.A5 (usb-c-pinout_CC1)
/2: /DN1: R14.1, U14.tp (p), U24.A7 (usb-c-pinout_DN1)
/2: /DN2: R5.1, U5.tp (p), U24.B7 (usb-c-pinout_DN2)
/2: /DP2: R4.1, U4.tp (p), U24.B6 (usb-c-pinout_DP2)
/2: /GND-usb: R18.1, U18.tp (p), U24.A1 (usb-c-pinout_GND), U24.A12 (usb-c-pinout_GND), U24.B1 (usb-c-pinout_GND), U24.B12 (usb-c-pinout_GND)
/2: /IN: R1.1, U1.tp (p), U24.B2 (usb-c-pinout_SSTXP2)
/2: /IN1: R13.1, U13.tp (p), U24.A6 (usb-c-pinout_DP1)
/2: /IN2: R9.1, U9.tp (p), U24.A2 (usb-c-pinout_SSTXP1)
/2: /IN3: R6.1, U6.tp (p), U24.B8 (usb-c-pinout_SBU2)
/2: /IN4: R17.1, U17.tp (p), U24.A11 (usb-c-pinout_SSRXP2)
/2: /IN5: R3.1, U3.tp (p), U24.B5 (usb-c-pinout_CC2)
/2: /IN6: R15.1, U15.tp (p), U24.A8 (usb-c-pinout_SBU1)
/2: /IN7: R7.1, U7.tp (p), U24.B10 (usb-c-pinout_SSRXN1)
/2: /POWER: B1.1 (power_vdd), U23.A1 (usb-c-pinout_GND), U23.A2 (usb-c-pinout_SSTXP1), U23.A3 (usb-c-pinout_SSTXN1), U23.A4 (usb-c-pinout_VBUS), U23.A5 (usb-c-pinout_CC1), U23.A6 (usb-c-pinout_DP1), U23.A7 (usb-c-pinout_DN1), U23.A8 (usb-c-pinout_SBU1), U23.A9 (usb-c-pinout_VBUS), U23.A10 (usb-c-pinout_SSRXN2), U23.A11 (usb-c-pinout_SSRXP2), U23.A12 (usb-c-pinout_GND), U23.B1 (usb-c-pinout_GND), U23.B2 (usb-c-pinout_SSTXP2), U23.B3 (usb-c-pinout_SSTXN2), U23.B4 (usb-c-pinout_VBUS), U23.B5 (usb-c-pinout_CC2), U23.B6 (usb-c-pinout_DP2), U23.B7 (usb-c-pinout_DN2), U23.B8 (usb-c-pinout_SBU2), U23.B9 (usb-c-pinout_VBUS), U23.B10 (usb-c-pinout_SSRXN1), U23.B11 (usb-c-pinout_SSRXP1), U23.B12 (usb-c-pinout_GND), U23.S1 (usb-c-pinout_shield), U23.S2 (usb-c-pinout_shield), U23.S3 (usb-c-pinout_shield), U23.S4 (usb-c-pinout_shield)
/2: /SSRXN2: R16.1, U16.tp (p), U24.A10 (usb-c-pinout_SSRXN2)
/2: /SSRXP1: R8.1, U8.tp (p), U24.B11 (usb-c-pinout_SSRXP1)
/2: /SSTXN1: R10.1, U10.tp (p), U24.A3 (usb-c-pinout_SSTXN1)
/2: /SSTXN2: R2.1, U2.tp (p), U24.B3 (usb-c-pinout_SSTXN2)
/2: /VBUS: R11.1, U11.tp (p), U24.A4 (usb-c-pinout_VBUS), U24.A9 (usb-c-pinout_VBUS), U24.B4 (usb-c-pinout_VBUS), U24.B9 (usb-c-pinout_VBUS)
unnamed: B1.2 (power_gnd), LED1.2 (c), LED2.2 (c), LED3.2 (c), LED4.2 (c), LED5.2 (c), LED6.2 (c), LED7.2 (c), LED8.2 (c), LED9.2 (c), LED10.2 (c), LED11.2 (c), LED12.2 (c), LED13.2 (c), LED14.2 (c), LED15.2 (c), LED16.2 (c), LED17.2 (c), LED18.2 (c)
unnamed: LED1.1 (a), R1.2
unnamed: LED2.1 (a), R2.2
unnamed: LED3.1 (a), R3.2
unnamed: LED4.1 (a), R4.2
unnamed: LED5.1 (a), R5.2
unnamed: LED6.1 (a), R6.2
unnamed: LED7.1 (a), R7.2
unnamed: LED8.1 (a), R8.2
unnamed: LED9.1 (a), R9.2
unnamed: LED10.1 (a), R10.2
unnamed: LED11.1 (a), R11.2
unnamed: LED12.1 (a), R12.2
unnamed: LED13.1 (a), R13.2
unnamed: LED14.1 (a), R14.2
unnamed: LED15.1 (a), R15.2
unnamed: LED16.1 (a), R16.2
unnamed: LED17.1 (a), R17.2
unnamed: LED18.1 (a), R18.2
unnamed: U24.S1 (usb-c-pinout_shield), U24.S2 (usb-c-pinout_shield), U24.S3 (usb-c-pinout_shield), U24.S4 (usb-c-pinout_shield)

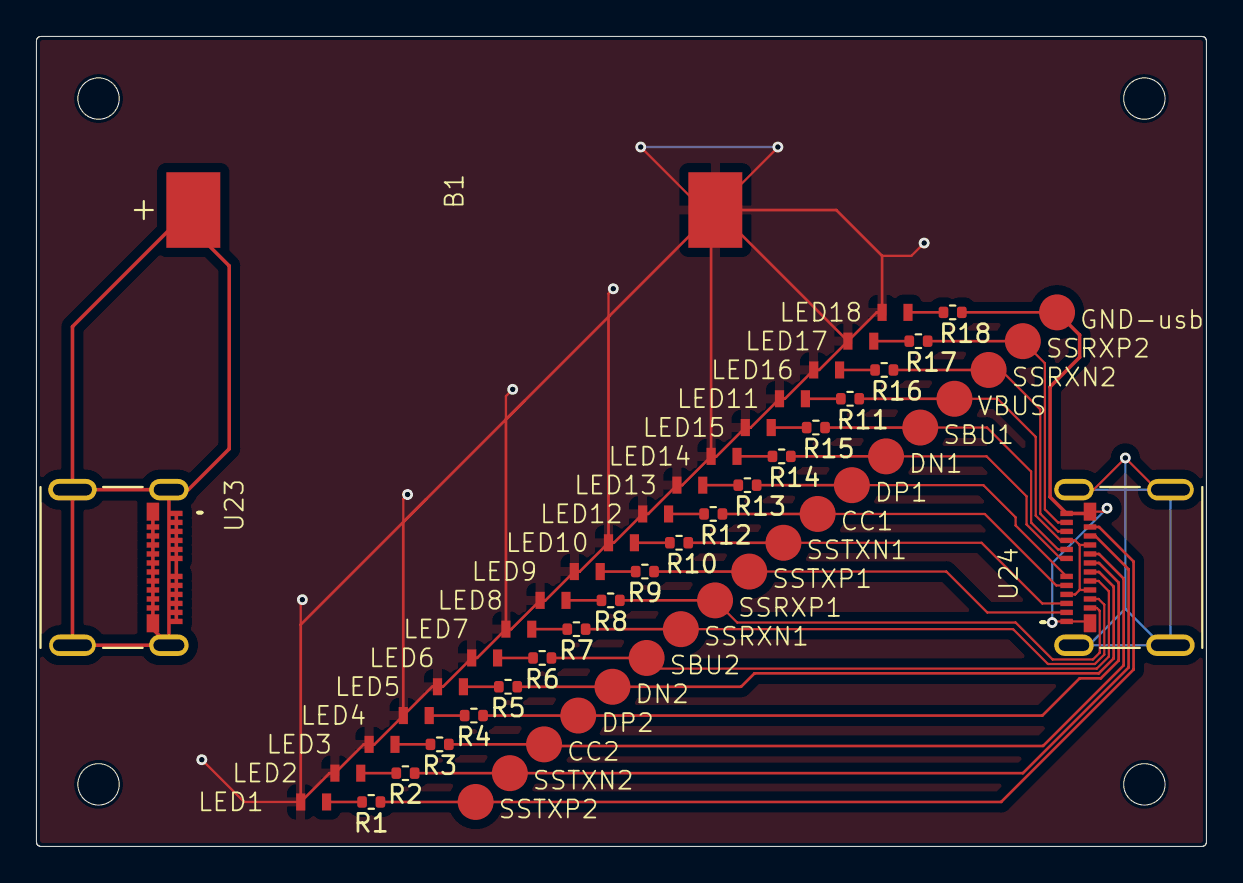
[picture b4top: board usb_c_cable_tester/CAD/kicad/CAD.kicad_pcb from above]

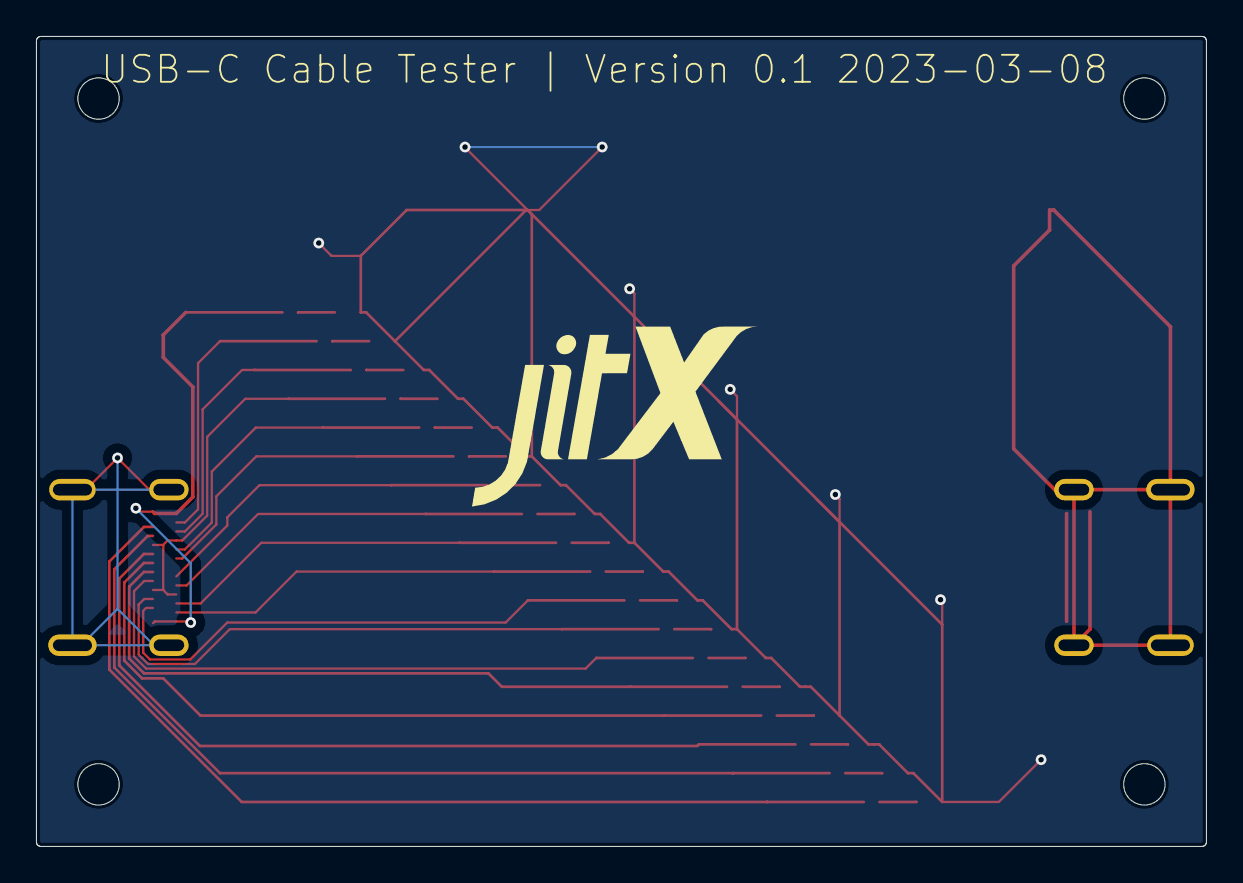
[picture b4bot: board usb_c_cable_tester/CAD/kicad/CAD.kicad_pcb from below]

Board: 2 copper layers, 65.0 x 45.0 mm, 81 parts (2 on the bottom side), 39 nets.
